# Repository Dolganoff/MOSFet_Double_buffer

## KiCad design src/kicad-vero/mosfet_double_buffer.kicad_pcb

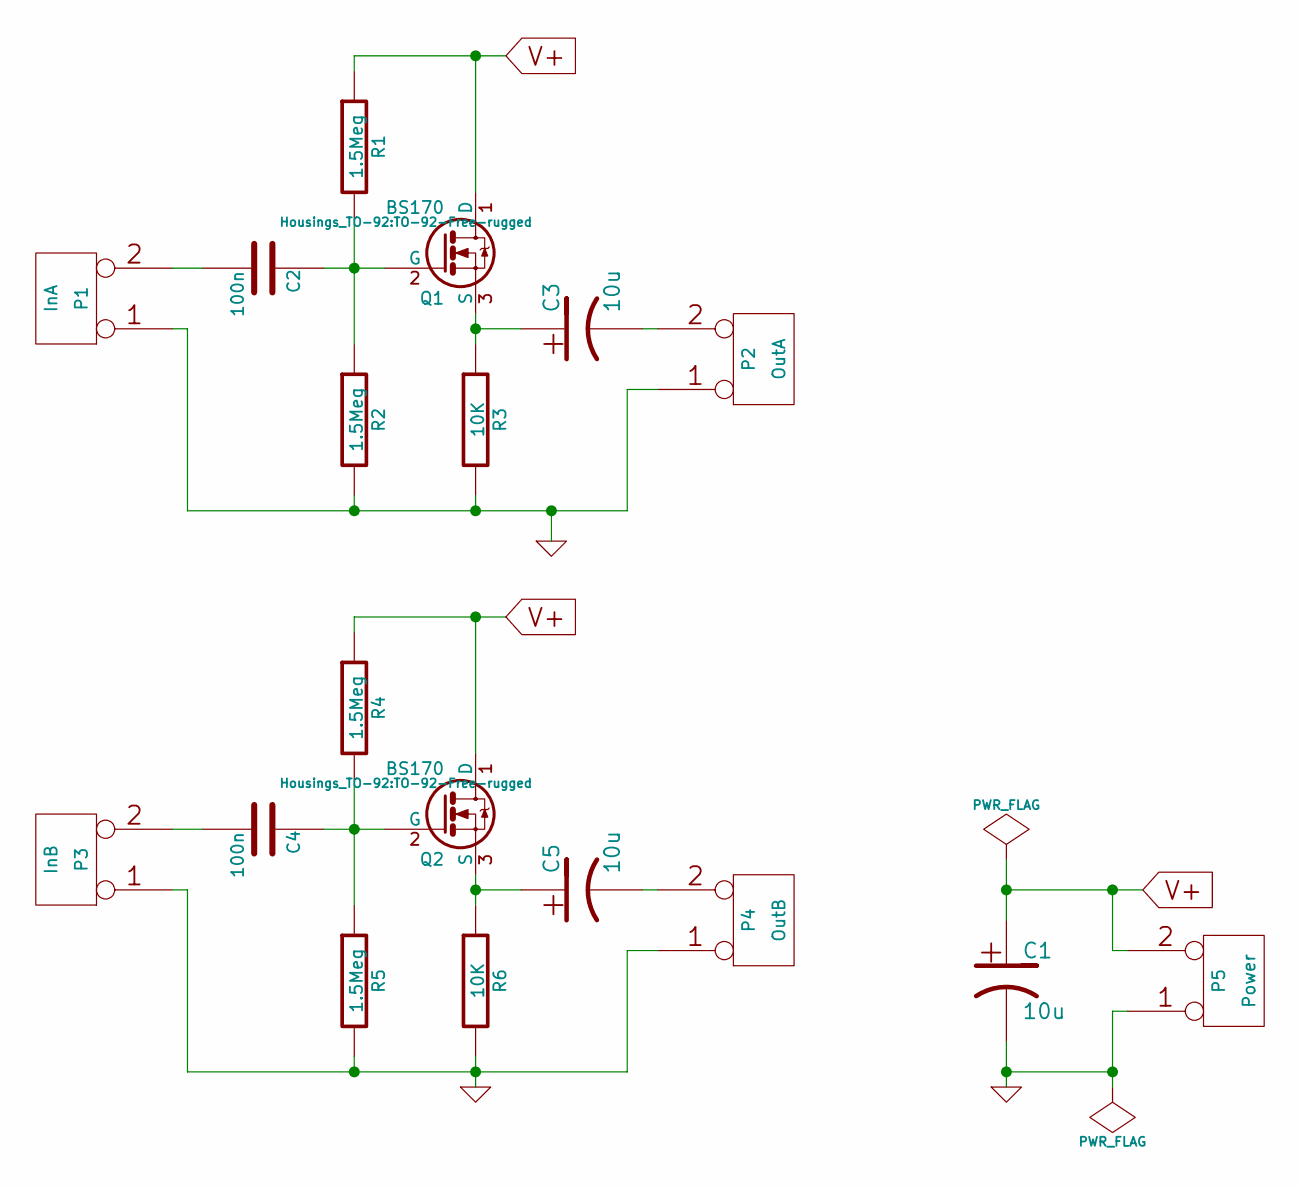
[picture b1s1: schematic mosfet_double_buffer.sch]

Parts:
C1, C3, C5: 10u; C1V5-LARGE_PADS
C2, C4: 100n; C2-LARGE_PADS
P1: InA; SIL-2-LARGE_PADS
P2: OutA; SIL-2-LARGE_PADS
P3: InB; SIL-2-LARGE_PADS
P4: OutB; SIL-2-LARGE_PADS
P5: Power; SIL-2-LARGE_PADS
Q1, Q2: BS170; TO-92-Free-rugged
R1, R4: 1.5Meg; R3-LARGE_PADS
R2, R5: 1.5Meg; R4-LARGE_PADS
R3, R6: 10K; R3-LARGE_PADS

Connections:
GND: C1.2, P1.1, P2.1, P3.1, P4.1, P5.1, R2.2, R3.2, R5.2, R6.2; also elsewhere on the board
unnamed: C2.1, Q1.2 (G), R1.2, R2.1
unnamed: C2.2, P1.2 (PM)
unnamed: C3.1, Q1.3 (S), R3.1
unnamed: C3.2, P2.2 (PM)
unnamed: C4.1, Q2.2 (G), R4.2, R5.1
unnamed 6: C4.2, P3.2 (PM); also elsewhere on the board
unnamed: C5.1, Q2.3 (S), R6.1
unnamed 8: C5.2, P4.2 (PM); also elsewhere on the board
V+: C1.1, P5.2 (PM), Q1.1 (D), Q2.1 (D), R1.1, R4.1

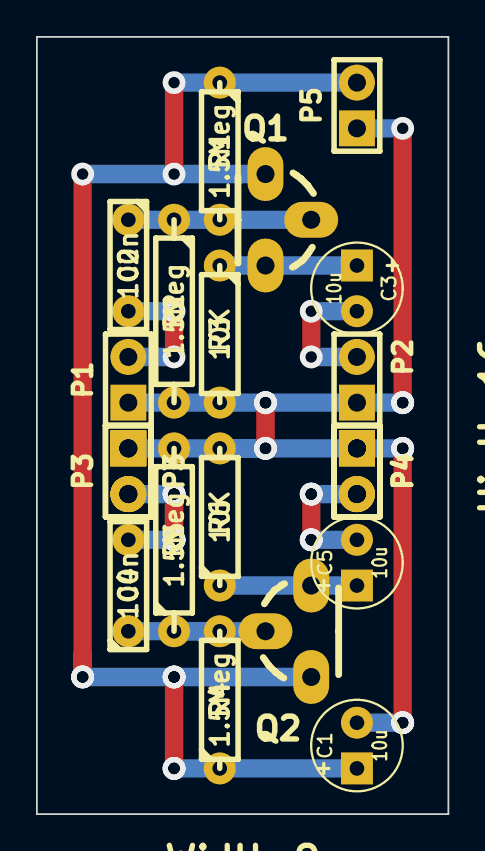
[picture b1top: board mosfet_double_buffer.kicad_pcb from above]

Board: 2 copper layers, 22.9 x 43.2 mm, 24 parts (0 on the bottom side), 10 nets.

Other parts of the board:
P3#2, P4#2: CONN_2; SIL-2-LARGE_PADS
o: track_drill
o#2, o#3, o#4: track_drill

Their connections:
GND: P3#2.1, P4#2.1; also elsewhere on the board
unnamed 6: P3#2.2; also elsewhere on the board
unnamed 8: P4#2.2; also elsewhere on the board

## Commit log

2015-01-11 :lollipop: Added .gitattributes & .gitignore files
2015-01-17 finalisation
